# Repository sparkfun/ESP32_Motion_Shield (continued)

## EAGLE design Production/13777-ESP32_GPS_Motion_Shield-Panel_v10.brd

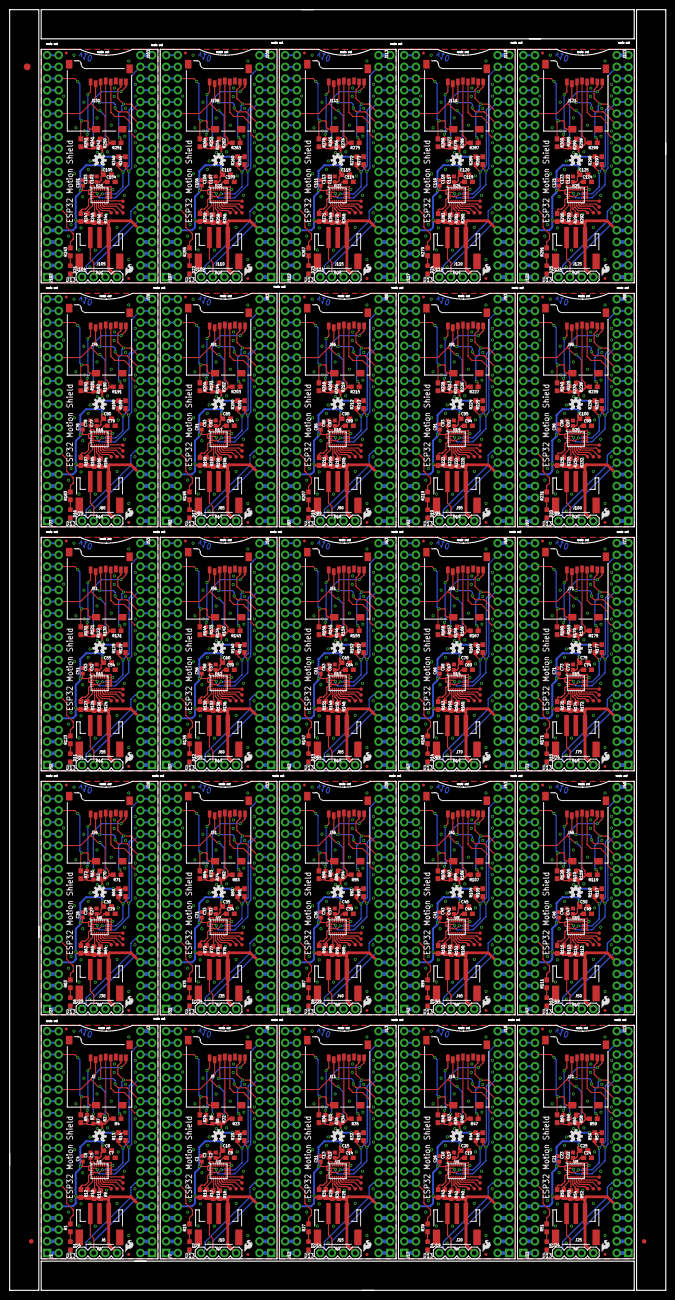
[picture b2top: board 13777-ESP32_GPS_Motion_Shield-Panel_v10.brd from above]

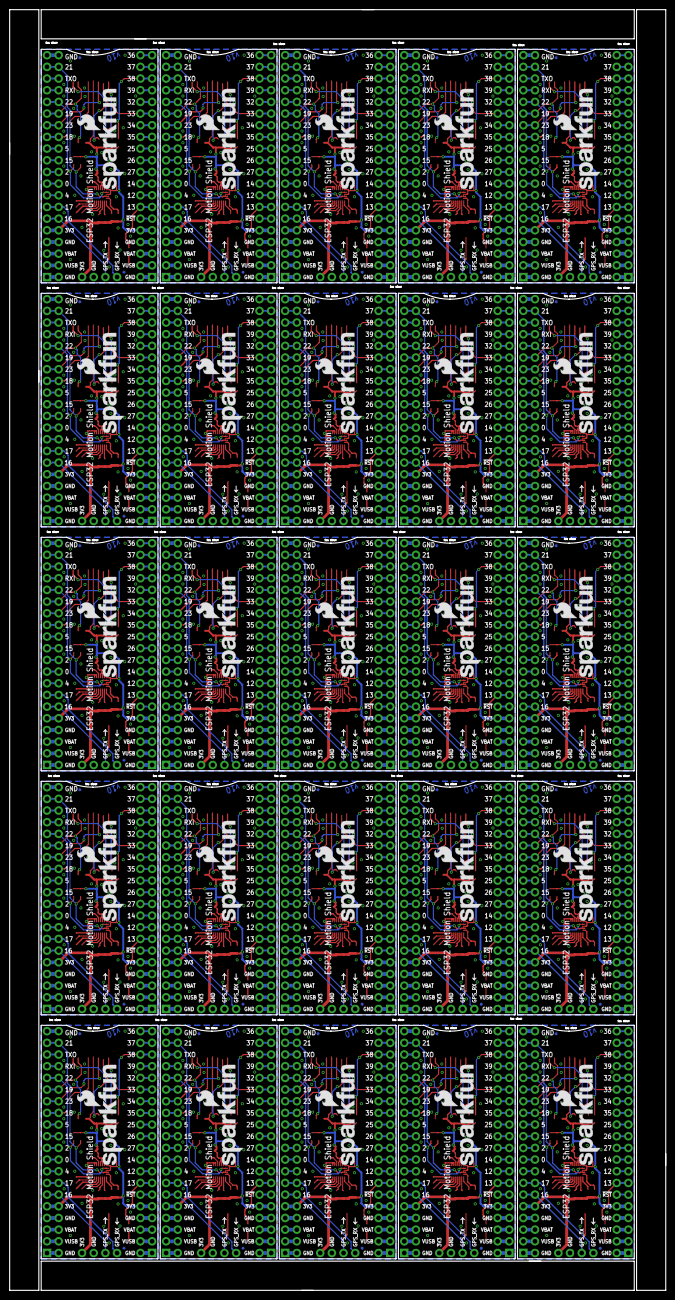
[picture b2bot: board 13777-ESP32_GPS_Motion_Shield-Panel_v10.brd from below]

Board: 2 copper layers, 142.7 x 278.6 mm, 928 parts (75 on the bottom side), 1225 nets.

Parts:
B1, B2, B3, B4, B5, B6, B7, B8, B9, B10, B11, B12, B13, B14, B15, B16, B17, B18, B19, B20, B21, B22, B23, B24, B25: ESP32_THING_WO_ANT_KEEPOUT; ESP32_THING_NO_ANT
C1, C2, C3, C4, C5, C6, C11, C12, C13, C16, C17, C18, C21, C22, C23, C26, C27, C28, C31, C32, C33, C36, C37, C38, C41, C42, C43, C46, C47, C48, C51, C52, C53, C56, C57, C58, C61, C62, C63, C66, C67, C68, C71, C72, C73, C76, C77, C78, C81, C82, C83, C86, C87, C88, C91, C92, C93, C96, C97, C98, C101, C102, C103, C106, C107, C108, C111, C112, C113, C116, C117, C118, C121, C122, C123: 0.1uF; 0402
C7, C9, C14, C19, C24, C29, C34, C39, C44, C49, C54, C59, C64, C69, C74, C79, C84, C89, C94, C99, C104, C109, C114, C119, C124: 10nF; 0603
C8, C10, C15, C20, C25, C30, C35, C40, C45, C50, C55, C60, C65, C70, C75, C80, C85, C90, C95, C100, C105, C110, C115, C120, C125: 10uF; 0603
D1, D2, D3, D4, D5, D6, D7, D8, D9, D10, D11, D12, D13, D14, D15, D16, D17, D18, D19, D20, D21, D22, D23, D24, D25: BLUE; LED-0603
E$1, E$2: FIDUCIAL-1X2
E$3: FIDUCIAL-1.5X3
FD1, FD2, FD3, FD4, FD5, FD6, FD7, FD8, FD9, FD10, FD11, FD12, FD13, FD14, FD15, FD16, FD17, FD18, FD19, FD20, FD21, FD22, FD23, FD24, FD25, FD26, FD27, FD28, FD29, FD30, FD31, FD32, FD33, FD34, FD35, FD36, FD37, FD38, FD39, FD40, FD41, FD42, FD43, FD44, FD45, FD46, FD47, FD48, FD49, FD50, FD51, FD52, FD53, FD54, FD55, FD56, FD57, FD58, FD59, FD60, FD61, FD62, FD63, FD64, FD65, FD66, FD67, FD68, FD69, FD70, FD71, FD72, FD73, FD74, FD75, FD76, FD77, FD78, FD79, FD80, FD81, FD82, FD83, FD84, FD85, FD86, FD87, FD88, FD89, FD90, FD91, FD92, FD93, FD94, FD95, FD96, FD97, FD98, FD99, FD100: FIDUCIALUFIDUCIAL; FIDUCIAL-MICRO
J1, J3, J7, J8, J12, J13, J17, J18, J22, J23, J27, J28, J32, J33, J37, J38, J42, J43, J47, J48, J52, J53, J57, J58, J62, J63, J67, J68, J72, J73, J77, J78, J82, J83, J87, J88, J92, J93, J97, J98, J102, J103, J107, J108, J112, J113, J117, J118, J122, J123: 1X20_NOSILK
J2, J5, J11, J16, J21, J26, J31, J36, J41, J46, J51, J56, J61, J66, J71, J76, J81, J86, J91, J96, J101, J106, J111, J116, J121: MICRO-SD_CARD_SOCKET; MICRO-SD-SOCKET
J4, J9, J14, J19, J24, J29, J34, J39, J44, J49, J54, J59, J64, J69, J74, J79, J84, J89, J94, J99, J104, J109, J114, J119, J124: 1X04
J6, J10, J15, J20, J25, J30, J35, J40, J45, J50, J55, J60, J65, J70, J75, J80, J85, J90, J95, J100, J105, J110, J115, J120, J125: 3-PIN SMD; JST-3-SMD
LOGO1, LOGO4, LOGO7, LOGO10, LOGO13, LOGO16, LOGO19, LOGO22, LOGO25, LOGO28, LOGO31, LOGO34, LOGO37, LOGO40, LOGO43, LOGO46, LOGO49, LOGO52, LOGO55, LOGO58, LOGO61, LOGO64, LOGO67, LOGO70, LOGO73: OSHW-LOGOS; OSHW-LOGO-S
LOGO2, LOGO6, LOGO9, LOGO12, LOGO15, LOGO18, LOGO21, LOGO24, LOGO27, LOGO30, LOGO33, LOGO36, LOGO39, LOGO42, LOGO45, LOGO48, LOGO51, LOGO54, LOGO57, LOGO60, LOGO63, LOGO66, LOGO69, LOGO72, LOGO75: SFE_LOGO_NAME_FLAME.2_INCH; SFE_LOGO_NAME_FLAME_.2
LOGO3, LOGO5, LOGO8, LOGO11, LOGO14, LOGO17, LOGO20, LOGO23, LOGO26, LOGO29, LOGO32, LOGO35, LOGO38, LOGO41, LOGO44, LOGO47, LOGO50, LOGO53, LOGO56, LOGO59, LOGO62, LOGO65, LOGO68, LOGO71, LOGO74: SFE_LOGO_FLAME.1_INCH; SFE_LOGO_FLAME_.1
R1, R15, R27, R39, R51, R63, R75, R87, R99, R111, R123, R135, R147, R159, R171, R183, R195, R207, R219, R231, R243, R255, R267, R279, R291: 470; 0603
R2, R4, R5, R9, R10, R11, R12, R16, R17, R18, R19, R22, R23, R24, R28, R29, R30, R31, R34, R35, R36, R40, R41, R42, R43, R46, R47, R48, R52, R53, R54, R55, R58, R59, R60, R64, R65, R66, R67, R70, R71, R72, R76, R77, R78, R79, R82, R83, R84, R88, R89, R90, R91, R94, R95, R96, R100, R101, R102, R103, R106, R107, R108, R112, R113, R114, R115, R118, R119, R120, R124, R125, R126, R127, R130, R131, R132, R136, R137, R138, R139, R142, R143, R144, R148, R149, R150, R151, R154, R155, R156, R160, R161, R162, R163, R166, R167, R168, R172, R173, R174, R175, R178, R179, R180, R184, R185, R186, R187, R190, R191, R192, R196, R197, R198, R199, R202, R203, R204, R208, R209, R210, R211, R214, R215, R216, R220, R221, R222, R223, R226, R227, R228, R232, R233, R234, R235, R238, R239, R240, R244, R245, R246, R247, R250, R251, R252, R256, R257, R258, R259, R262, R263, R264, R268, R269, R270, R271, R274, R275, R276, R280, R281, R282, R283, R286, R287, R288, R292, R293, R294, R295, R298, R299, R300: 10k; 0603
R3, R6, R7, R8, R25, R26, R37, R38, R49, R50, R61, R62, R73, R74, R85, R86, R97, R98, R109, R110, R121, R122, R133, R134, R145, R146, R157, R158, R169, R170, R181, R182, R193, R194, R205, R206, R217, R218, R229, R230, R241, R242, R253, R254, R265, R266, R277, R278, R289, R290: 100K; 0402
R13, R14, R20, R21, R32, R33, R44, R45, R56, R57, R68, R69, R80, R81, R92, R93, R104, R105, R116, R117, R128, R129, R140, R141, R152, R153, R164, R165, R176, R177, R188, R189, R200, R201, R212, R213, R224, R225, R236, R237, R248, R249, R260, R261, R272, R273, R284, R285, R296, R297: 4.7k; 0603
TP1, TP2, TP3, TP4, TP5, TP6, TP7, TP8, TP9, TP10, TP11, TP12, TP13, TP14, TP15, TP16, TP17, TP18, TP19, TP20, TP21, TP22, TP23, TP24, TP25, TP26, TP27, TP28, TP29, TP30, TP31, TP32, TP33, TP34, TP35, TP36, TP37, TP38, TP39, TP40, TP41, TP42, TP43, TP44, TP45, TP46, TP47, TP48, TP49, TP50, TP51, TP52, TP53, TP54, TP55, TP56, TP57, TP58, TP59, TP60, TP61, TP62, TP63, TP64, TP65, TP66, TP67, TP68, TP69, TP70, TP71, TP72, TP73, TP74, TP75, TP76, TP77, TP78, TP79, TP80, TP81, TP82, TP83, TP84, TP85, TP86, TP87, TP88, TP89, TP90, TP91, TP92, TP93, TP94, TP95, TP96, TP97, TP98, TP99, TP100, TP101, TP102, TP103, TP104, TP105, TP106, TP107, TP108, TP109, TP110, TP111, TP112, TP113, TP114, TP115, TP116, TP117, TP118, TP119, TP120, TP121, TP122, TP123, TP124, TP125: TEST-POINT3; PAD.03X.03
U1, U2, U3, U4, U5, U6, U7, U8, U9, U10, U11, U12, U13, U14, U15, U16, U17, U18, U19, U20, U21, U22, U23, U24, U25: LSM9DS1; LGA-24-3.5X3

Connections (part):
3.3V: B1.5, B1.36, C4.1, C5.1, C8.1, J1.5, J2.VCC, J3.16, J4.4, J6.3, R2.2, R3.2, R4.2, R5.2, R7.2, R9.2, R10.2, R11.2, R12.2, R13.2, R14.2, U1.1, U1.3, U1.22, U1.23
3.3V1: B2.5, B2.36, C1.1, C2.1, C10.1, J5.VCC, J7.5, J8.16, J9.4, J10.3, R6.2, R8.2, R16.2, R17.2, R18.2, R19.2, R20.2, R21.2, R22.2, R23.2, R24.2, U2.1, U2.3, U2.22, U2.23
3.3V2: B3.5, B3.36, C11.1, C12.1, C15.1, J11.VCC, J12.5, J13.16, J14.4, J15.3, R25.2, R26.2, R28.2, R29.2, R30.2, R31.2, R32.2, R33.2, R34.2, R35.2, R36.2, U3.1, U3.3, U3.22, U3.23
3.3V3: B4.5, B4.36, C16.1, C17.1, C20.1, J16.VCC, J17.5, J18.16, J19.4, J20.3, R37.2, R38.2, R40.2, R41.2, R42.2, R43.2, R44.2, R45.2, R46.2, R47.2, R48.2, U4.1, U4.3, U4.22, U4.23
3.3V4: B5.5, B5.36, C21.1, C22.1, C25.1, J21.VCC, J22.5, J23.16, J24.4, J25.3, R49.2, R50.2, R52.2, R53.2, R54.2, R55.2, R56.2, R57.2, R58.2, R59.2, R60.2, U5.1, U5.3, U5.22, U5.23
3.3V5: B6.5, B6.36, C26.1, C27.1, C30.1, J26.VCC, J27.5, J28.16, J29.4, J30.3, R61.2, R62.2, R64.2, R65.2, R66.2, R67.2, R68.2, R69.2, R70.2, R71.2, R72.2, U6.1, U6.3, U6.22, U6.23
3.3V6: B7.5, B7.36, C31.1, C32.1, C35.1, J31.VCC, J32.5, J33.16, J34.4, J35.3, R73.2, R74.2, R76.2, R77.2, R78.2, R79.2, R80.2, R81.2, R82.2, R83.2, R84.2, U7.1, U7.3, U7.22, U7.23
3.3V7: B8.5, B8.36, C36.1, C37.1, C40.1, J36.VCC, J37.5, J38.16, J39.4, J40.3, R85.2, R86.2, R88.2, R89.2, R90.2, R91.2, R92.2, R93.2, R94.2, R95.2, R96.2, U8.1, U8.3, U8.22, U8.23
3.3V8: B9.5, B9.36, C41.1, C42.1, C45.1, J41.VCC, J42.5, J43.16, J44.4, J45.3, R97.2, R98.2, R100.2, R101.2, R102.2, R103.2, R104.2, R105.2, R106.2, R107.2, R108.2, U9.1, U9.3, U9.22, U9.23
3.3V9: B10.5, B10.36, C46.1, C47.1, C50.1, J46.VCC, J47.5, J48.16, J49.4, J50.3, R109.2, R110.2, R112.2, R113.2, R114.2, R115.2, R116.2, R117.2, R118.2, R119.2, R120.2, U10.1, U10.3, U10.22, U10.23
3.3V10: B11.5, B11.36, C51.1, C52.1, C55.1, J51.VCC, J52.5, J53.16, J54.4, J55.3, R121.2, R122.2, R124.2, R125.2, R126.2, R127.2, R128.2, R129.2, R130.2, R131.2, R132.2, U11.1, U11.3, U11.22, U11.23
3.3V11: B12.5, B12.36, C56.1, C57.1, C60.1, J56.VCC, J57.5, J58.16, J59.4, J60.3, R133.2, R134.2, R136.2, R137.2, R138.2, R139.2, R140.2, R141.2, R142.2, R143.2, R144.2, U12.1, U12.3, U12.22, U12.23
3.3V12: B13.5, B13.36, C61.1, C62.1, C65.1, J61.VCC, J62.5, J63.16, J64.4, J65.3, R145.2, R146.2, R148.2, R149.2, R150.2, R151.2, R152.2, R153.2, R154.2, R155.2, R156.2, U13.1, U13.3, U13.22, U13.23
3.3V13: B14.5, B14.36, C66.1, C67.1, C70.1, J66.VCC, J67.5, J68.16, J69.4, J70.3, R157.2, R158.2, R160.2, R161.2, R162.2, R163.2, R164.2, R165.2, R166.2, R167.2, R168.2, U14.1, U14.3, U14.22, U14.23
3.3V14: B15.5, B15.36, C71.1, C72.1, C75.1, J71.VCC, J72.5, J73.16, J74.4, J75.3, R169.2, R170.2, R172.2, R173.2, R174.2, R175.2, R176.2, R177.2, R178.2, R179.2, R180.2, U15.1, U15.3, U15.22, U15.23
3.3V15: B16.5, B16.36, C76.1, C77.1, C80.1, J76.VCC, J77.5, J78.16, J79.4, J80.3, R181.2, R182.2, R184.2, R185.2, R186.2, R187.2, R188.2, R189.2, R190.2, R191.2, R192.2, U16.1, U16.3, U16.22, U16.23
3.3V16: B17.5, B17.36, C81.1, C82.1, C85.1, J81.VCC, J82.5, J83.16, J84.4, J85.3, R193.2, R194.2, R196.2, R197.2, R198.2, R199.2, R200.2, R201.2, R202.2, R203.2, R204.2, U17.1, U17.3, U17.22, U17.23
3.3V17: B18.5, B18.36, C86.1, C87.1, C90.1, J86.VCC, J87.5, J88.16, J89.4, J90.3, R205.2, R206.2, R208.2, R209.2, R210.2, R211.2, R212.2, R213.2, R214.2, R215.2, R216.2, U18.1, U18.3, U18.22, U18.23
3.3V18: B19.5, B19.36, C91.1, C92.1, C95.1, J91.VCC, J92.5, J93.16, J94.4, J95.3, R217.2, R218.2, R220.2, R221.2, R222.2, R223.2, R224.2, R225.2, R226.2, R227.2, R228.2, U19.1, U19.3, U19.22, U19.23
3.3V19: B20.5, B20.36, C96.1, C97.1, C100.1, J96.VCC, J97.5, J98.16, J99.4, J100.3, R229.2, R230.2, R232.2, R233.2, R234.2, R235.2, R236.2, R237.2, R238.2, R239.2, R240.2, U20.1, U20.3, U20.22, U20.23
3.3V20: B21.5, B21.36, C101.1, C102.1, C105.1, J101.VCC, J102.5, J103.16, J104.4, J105.3, R241.2, R242.2, R244.2, R245.2, R246.2, R247.2, R248.2, R249.2, R250.2, R251.2, R252.2, U21.1, U21.3, U21.22, U21.23
3.3V21: B22.5, B22.36, C106.1, C107.1, C110.1, J106.VCC, J107.5, J108.16, J109.4, J110.3, R253.2, R254.2, R256.2, R257.2, R258.2, R259.2, R260.2, R261.2, R262.2, R263.2, R264.2, U22.1, U22.3, U22.22, U22.23
3.3V22: B23.5, B23.36, C111.1, C112.1, C115.1, J111.VCC, J112.5, J113.16, J114.4, J115.3, R265.2, R266.2, R268.2, R269.2, R270.2, R271.2, R272.2, R273.2, R274.2, R275.2, R276.2, U23.1, U23.3, U23.22, U23.23
3.3V23: B24.5, B24.36, C116.1, C117.1, C120.1, J116.VCC, J117.5, J118.16, J119.4, J120.3, R277.2, R278.2, R280.2, R281.2, R282.2, R283.2, R284.2, R285.2, R286.2, R287.2, R288.2, U24.1, U24.3, U24.22, U24.23
3.3V24: B25.5, B25.36, C121.1, C122.1, C125.1, J121.VCC, J122.5, J123.16, J124.4, J125.3, R289.2, R290.2, R292.2, R293.2, R294.2, R295.2, R296.2, R297.2, R298.2, R299.2, R300.2, U25.1, U25.3, U25.22, U25.23
C1: C6.1, U1.24
C2: C3.1, U2.24
C3: C13.1, U3.24
C4: C18.1, U4.24
C5: C23.1, U5.24
C6: C28.1, U6.24
C7: C33.1, U7.24
C8: C38.1, U8.24
C9: C43.1, U9.24
C10: C48.1, U10.24
C11: C53.1, U11.24
C12: C58.1, U12.24
C13: C63.1, U13.24
C14: C68.1, U14.24
C15: C73.1, U15.24
C16: C78.1, U16.24
C17: C83.1, U17.24
C18: C88.1, U18.24
C19: C93.1, U19.24
C20: C98.1, U20.24
C21: C103.1, U21.24
C22: C108.1, U22.24
C23: C113.1, U23.24
C24: C118.1, U24.24
C25: C123.1, U25.24
CAP: C7.1, U1.21
CAP1: C9.1, U2.21
CAP2: C14.1, U3.21
CAP3: C19.1, U4.21
CAP4: C24.1, U5.21
CAP5: C29.1, U6.21
CAP6: C34.1, U7.21
CAP7: C39.1, U8.21
CAP8: C44.1, U9.21
CAP9: C49.1, U10.21
CAP10: C54.1, U11.21
CAP11: C59.1, U12.21
CAP12: C64.1, U13.21
CAP13: C69.1, U14.21
CAP14: C74.1, U15.21
CAP15: C79.1, U16.21
CAP16: C84.1, U17.21
CAP17: C89.1, U18.21
CAP18: C94.1, U19.21
CAP19: C99.1, U20.21
CAP20: C104.1, U21.21
CAP21: C109.1, U22.21
CAP22: C114.1, U23.21
CAP23: C119.1, U24.21
CAP24: C124.1, U25.21
CS_A/G: R11.1, U1.7
CS_A/G1: R18.1, U2.7
CS_A/G2: R30.1, U3.7
CS_A/G3: R42.1, U4.7
CS_A/G4: R54.1, U5.7
CS_A/G5: R66.1, U6.7
CS_A/G6: R78.1, U7.7
CS_A/G7: R90.1, U8.7
CS_A/G8: R102.1, U9.7
CS_A/G9: R114.1, U10.7
CS_A/G10: R126.1, U11.7
CS_A/G11: R138.1, U12.7
CS_A/G12: R150.1, U13.7
CS_A/G13: R162.1, U14.7
CS_A/G14: R174.1, U15.7
CS_A/G15: R186.1, U16.7
CS_A/G16: R198.1, U17.7
CS_A/G17: R210.1, U18.7
CS_A/G18: R222.1, U19.7
CS_A/G19: R234.1, U20.7
CS_A/G20: R246.1, U21.7
CS_A/G21: R258.1, U22.7
CS_A/G22: R270.1, U23.7
CS_A/G23: R282.1, U24.7
CS_A/G24: R294.1, U25.7
CS_M: R9.1, U1.8
CS_M1: R16.1, U2.8
CS_M2: R28.1, U3.8
CS_M3: R40.1, U4.8
CS_M4: R52.1, U5.8
CS_M5: R64.1, U6.8
CS_M6: R76.1, U7.8
CS_M7: R88.1, U8.8
CS_M8: R100.1, U9.8
CS_M9: R112.1, U10.8
CS_M10: R124.1, U11.8
CS_M11: R136.1, U12.8
CS_M12: R148.1, U13.8
CS_M13: R160.1, U14.8
CS_M14: R172.1, U15.8
CS_M15: R184.1, U16.8
CS_M16: R196.1, U17.8
CS_M17: R208.1, U18.8
CS_M18: R220.1, U19.8
CS_M19: R232.1, U20.8
CS_M20: R244.1, U21.8
CS_M21: R256.1, U22.8
CS_M22: R268.1, U23.8
CS_M23: R280.1, U24.8
CS_M24: R292.1, U25.8
DEN_A/G: TP3.P$1, U1.13
DEN_A/G1: TP8.P$1, U2.13
DEN_A/G2: TP13.P$1, U3.13
DEN_A/G3: TP18.P$1, U4.13
DEN_A/G4: TP23.P$1, U5.13
DEN_A/G5: TP28.P$1, U6.13
DEN_A/G6: TP33.P$1, U7.13
DEN_A/G7: TP38.P$1, U8.13
DEN_A/G8: TP43.P$1, U9.13
DEN_A/G9: TP48.P$1, U10.13
DEN_A/G10: TP53.P$1, U11.13
DEN_A/G11: TP58.P$1, U12.13
DEN_A/G12: TP63.P$1, U13.13
DEN_A/G13: TP68.P$1, U14.13
DEN_A/G14: TP73.P$1, U15.13
DEN_A/G15: TP78.P$1, U16.13
DEN_A/G16: TP83.P$1, U17.13
DEN_A/G17: TP88.P$1, U18.13
DEN_A/G18: TP93.P$1, U19.13
DEN_A/G19: TP98.P$1, U20.13
DEN_A/G20: TP103.P$1, U21.13
DEN_A/G21: TP108.P$1, U22.13
DEN_A/G22: TP113.P$1, U23.13
DEN_A/G23: TP118.P$1, U24.13
DEN_A/G24: TP123.P$1, U25.13
DRDY_M: TP4.P$1, U1.9
DRDY_M1: TP9.P$1, U2.9
DRDY_M2: TP14.P$1, U3.9
DRDY_M3: TP19.P$1, U4.9
DRDY_M4: TP24.P$1, U5.9
DRDY_M5: TP29.P$1, U6.9
DRDY_M6: TP34.P$1, U7.9
DRDY_M7: TP39.P$1, U8.9
DRDY_M8: TP44.P$1, U9.9
DRDY_M9: TP49.P$1, U10.9
DRDY_M10: TP54.P$1, U11.9
DRDY_M11: TP59.P$1, U12.9
DRDY_M12: TP64.P$1, U13.9
DRDY_M13: TP69.P$1, U14.9
DRDY_M14: TP74.P$1, U15.9
DRDY_M15: TP79.P$1, U16.9
DRDY_M16: TP84.P$1, U17.9
DRDY_M17: TP89.P$1, U18.9
DRDY_M18: TP94.P$1, U19.9
DRDY_M19: TP99.P$1, U20.9
DRDY_M20: TP104.P$1, U21.9
DRDY_M21: TP109.P$1, U22.9
DRDY_M22: TP114.P$1, U23.9
DRDY_M23: TP119.P$1, U24.9
DRDY_M24: TP124.P$1, U25.9
GND: B1.1, B1.4, B1.21, B1.37, B1.40, C4.2, C5.2, C6.2, C7.2, C8.2, D1.C, J1.1, J1.4, J2.GND, J2.GND1, J2.GND3, J3.1, J3.17, J3.20, J4.3, J6.2, U1.14, U1.15, U1.16, U1.17, U1.18, U1.19, U1.20
GND1: B2.1, B2.4, B2.21, B2.37, B2.40, C1.2, C2.2, C3.2, C9.2, C10.2, D2.C, J5.GND, J5.GND1, J5.GND3, J7.1, J7.4, J8.1, J8.17, J8.20, J9.3, J10.2, U2.14, U2.15, U2.16, U2.17, U2.18, U2.19, U2.20
GND2: B3.1, B3.4, B3.21, B3.37, B3.40, C11.2, C12.2, C13.2, C14.2, C15.2, D3.C, J11.GND, J11.GND1, J11.GND3, J12.1, J12.4, J13.1, J13.17, J13.20, J14.3, J15.2, U3.14, U3.15, U3.16, U3.17, U3.18, U3.19, U3.20
GND3: B4.1, B4.4, B4.21, B4.37, B4.40, C16.2, C17.2, C18.2, C19.2, C20.2, D4.C, J16.GND, J16.GND1, J16.GND3, J17.1, J17.4, J18.1, J18.17, J18.20, J19.3, J20.2, U4.14, U4.15, U4.16, U4.17, U4.18, U4.19, U4.20
GND4: B5.1, B5.4, B5.21, B5.37, B5.40, C21.2, C22.2, C23.2, C24.2, C25.2, D5.C, J21.GND, J21.GND1, J21.GND3, J22.1, J22.4, J23.1, J23.17, J23.20, J24.3, J25.2, U5.14, U5.15, U5.16, U5.17, U5.18, U5.19, U5.20
GND5: B6.1, B6.4, B6.21, B6.37, B6.40, C26.2, C27.2, C28.2, C29.2, C30.2, D6.C, J26.GND, J26.GND1, J26.GND3, J27.1, J27.4, J28.1, J28.17, J28.20, J29.3, J30.2, U6.14, U6.15, U6.16, U6.17, U6.18, U6.19, U6.20
GND6: B7.1, B7.4, B7.21, B7.37, B7.40, C31.2, C32.2, C33.2, C34.2, C35.2, D7.C, J31.GND, J31.GND1, J31.GND3, J32.1, J32.4, J33.1, J33.17, J33.20, J34.3, J35.2, U7.14, U7.15, U7.16, U7.17, U7.18, U7.19, U7.20
GND7: B8.1, B8.4, B8.21, B8.37, B8.40, C36.2, C37.2, C38.2, C39.2, C40.2, D8.C, J36.GND, J36.GND1, J36.GND3, J37.1, J37.4, J38.1, J38.17, J38.20, J39.3, J40.2, U8.14, U8.15, U8.16, U8.17, U8.18, U8.19, U8.20
GND8: B9.1, B9.4, B9.21, B9.37, B9.40, C41.2, C42.2, C43.2, C44.2, C45.2, D9.C, J41.GND, J41.GND1, J41.GND3, J42.1, J42.4, J43.1, J43.17, J43.20, J44.3, J45.2, U9.14, U9.15, U9.16, U9.17, U9.18, U9.19, U9.20
GND9: B10.1, B10.4, B10.21, B10.37, B10.40, C46.2, C47.2, C48.2, C49.2, C50.2, D10.C, J46.GND, J46.GND1, J46.GND3, J47.1, J47.4, J48.1, J48.17, J48.20, J49.3, J50.2, U10.14, U10.15, U10.16, U10.17, U10.18, U10.19, U10.20
GND10: B11.1, B11.4, B11.21, B11.37, B11.40, C51.2, C52.2, C53.2, C54.2, C55.2, D11.C, J51.GND, J51.GND1, J51.GND3, J52.1, J52.4, J53.1, J53.17, J53.20, J54.3, J55.2, U11.14, U11.15, U11.16, U11.17, U11.18, U11.19, U11.20
GND11: B12.1, B12.4, B12.21, B12.37, B12.40, C56.2, C57.2, C58.2, C59.2, C60.2, D12.C, J56.GND, J56.GND1, J56.GND3, J57.1, J57.4, J58.1, J58.17, J58.20, J59.3, J60.2, U12.14, U12.15, U12.16, U12.17, U12.18, U12.19, U12.20
GND12: B13.1, B13.4, B13.21, B13.37, B13.40, C61.2, C62.2, C63.2, C64.2, C65.2, D13.C, J61.GND, J61.GND1, J61.GND3, J62.1, J62.4, J63.1, J63.17, J63.20, J64.3, J65.2, U13.14, U13.15, U13.16, U13.17, U13.18, U13.19, U13.20
GND13: B14.1, B14.4, B14.21, B14.37, B14.40, C66.2, C67.2, C68.2, C69.2, C70.2, D14.C, J66.GND, J66.GND1, J66.GND3, J67.1, J67.4, J68.1, J68.17, J68.20, J69.3, J70.2, U14.14, U14.15, U14.16, U14.17, U14.18, U14.19, U14.20
GND14: B15.1, B15.4, B15.21, B15.37, B15.40, C71.2, C72.2, C73.2, C74.2, C75.2, D15.C, J71.GND, J71.GND1, J71.GND3, J72.1, J72.4, J73.1, J73.17, J73.20, J74.3, J75.2, U15.14, U15.15, U15.16, U15.17, U15.18, U15.19, U15.20
GND15: B16.1, B16.4, B16.21, B16.37, B16.40, C76.2, C77.2, C78.2, C79.2, C80.2, D16.C, J76.GND, J76.GND1, J76.GND3, J77.1, J77.4, J78.1, J78.17, J78.20, J79.3, J80.2, U16.14, U16.15, U16.16, U16.17, U16.18, U16.19, U16.20
GND16: B17.1, B17.4, B17.21, B17.37, B17.40, C81.2, C82.2, C83.2, C84.2, C85.2, D17.C, J81.GND, J81.GND1, J81.GND3, J82.1, J82.4, J83.1, J83.17, J83.20, J84.3, J85.2, U17.14, U17.15, U17.16, U17.17, U17.18, U17.19, U17.20
GND17: B18.1, B18.4, B18.21, B18.37, B18.40, C86.2, C87.2, C88.2, C89.2, C90.2, D18.C, J86.GND, J86.GND1, J86.GND3, J87.1, J87.4, J88.1, J88.17, J88.20, J89.3, J90.2, U18.14, U18.15, U18.16, U18.17, U18.18, U18.19, U18.20
GND18: B19.1, B19.4, B19.21, B19.37, B19.40, C91.2, C92.2, C93.2, C94.2, C95.2, D19.C, J91.GND, J91.GND1, J91.GND3, J92.1, J92.4, J93.1, J93.17, J93.20, J94.3, J95.2, U19.14, U19.15, U19.16, U19.17, U19.18, U19.19, U19.20
GND19: B20.1, B20.4, B20.21, B20.37, B20.40, C96.2, C97.2, C98.2, C99.2, C100.2, D20.C, J96.GND, J96.GND1, J96.GND3, J97.1, J97.4, J98.1, J98.17, J98.20, J99.3, J100.2, U20.14, U20.15, U20.16, U20.17, U20.18, U20.19, U20.20
GND20: B21.1, B21.4, B21.21, B21.37, B21.40, C101.2, C102.2, C103.2, C104.2, C105.2, D21.C, J101.GND, J101.GND1, J101.GND3, J102.1, J102.4, J103.1, J103.17, J103.20, J104.3, J105.2, U21.14, U21.15, U21.16, U21.17, U21.18, U21.19, U21.20
GND21: B22.1, B22.4, B22.21, B22.37, B22.40, C106.2, C107.2, C108.2, C109.2, C110.2, D22.C, J106.GND, J106.GND1, J106.GND3, J107.1, J107.4, J108.1, J108.17, J108.20, J109.3, J110.2, U22.14, U22.15, U22.16, U22.17, U22.18, U22.19, U22.20
GND22: B23.1, B23.4, B23.21, B23.37, B23.40, C111.2, C112.2, C113.2, C114.2, C115.2, D23.C, J111.GND, J111.GND1, J111.GND3, J112.1, J112.4, J113.1, J113.17, J113.20, J114.3, J115.2, U23.14, U23.15, U23.16, U23.17, U23.18, U23.19, U23.20
GND23: B24.1, B24.4, B24.21, B24.37, B24.40, C116.2, C117.2, C118.2, C119.2, C120.2, D24.C, J116.GND, J116.GND1, J116.GND3, J117.1, J117.4, J118.1, J118.17, J118.20, J119.3, J120.2, U24.14, U24.15, U24.16, U24.17, U24.18, U24.19, U24.20
GND24: B25.1, B25.4, B25.21, B25.37, B25.40, C121.2, C122.2, C123.2, C124.2, C125.2, D25.C, J121.GND, J121.GND1, J121.GND3, J122.1, J122.4, J123.1, J123.17, J123.20, J124.3, J125.2, U25.14, U25.15, U25.16, U25.17, U25.18, U25.19, U25.20
GPS_LED: B1.7, J1.7, R1.2
GPS_LED1: B2.7, J7.7, R15.2
GPS_LED2: B3.7, J12.7, R27.2
GPS_LED3: B4.7, J17.7, R39.2
GPS_LED4: B5.7, J22.7, R51.2
GPS_LED5: B6.7, J27.7, R63.2
GPS_LED6: B7.7, J32.7, R75.2
GPS_LED7: B8.7, J37.7, R87.2
GPS_LED8: B9.7, J42.7, R99.2
GPS_LED9: B10.7, J47.7, R111.2
GPS_LED10: B11.7, J52.7, R123.2
GPS_LED11: B12.7, J57.7, R135.2
GPS_LED12: B13.7, J62.7, R147.2
GPS_LED13: B14.7, J67.7, R159.2
GPS_LED14: B15.7, J72.7, R171.2
GPS_LED15: B16.7, J77.7, R183.2
GPS_LED16: B17.7, J82.7, R195.2
GPS_LED17: B18.7, J87.7, R207.2
GPS_LED18: B19.7, J92.7, R219.2
GPS_LED19: B20.7, J97.7, R231.2
GPS_LED20: B21.7, J102.7, R243.2
GPS_LED21: B22.7, J107.7, R255.2
GPS_LED22: B23.7, J112.7, R267.2
GPS_LED23: B24.7, J117.7, R279.2
GPS_LED24: B25.7, J122.7, R291.2
GPS_RX: B1.34, J3.14, J4.1
GPS_RX1: B2.34, J8.14, J9.1
GPS_RX2: B3.34, J13.14, J14.1
GPS_RX3: B4.34, J18.14, J19.1
GPS_RX4: B5.34, J23.14, J24.1
GPS_RX5: B6.34, J28.14, J29.1
GPS_RX6: B7.34, J33.14, J34.1
GPS_RX7: B8.34, J38.14, J39.1
GPS_RX8: B9.34, J43.14, J44.1
GPS_RX9: B10.34, J48.14, J49.1
GPS_RX10: B11.34, J53.14, J54.1
GPS_RX11: B12.34, J58.14, J59.1
GPS_RX12: B13.34, J63.14, J64.1
GPS_RX13: B14.34, J68.14, J69.1
GPS_RX14: B15.34, J73.14, J74.1
GPS_RX15: B16.34, J78.14, J79.1
GPS_RX16: B17.34, J83.14, J84.1
GPS_RX17: B18.34, J88.14, J89.1
GPS_RX18: B19.34, J93.14, J94.1
GPS_RX19: B20.34, J98.14, J99.1
GPS_RX20: B21.34, J103.14, J104.1
GPS_RX21: B22.34, J108.14, J109.1
GPS_RX22: B23.34, J113.14, J114.1
GPS_RX23: B24.34, J118.14, J119.1
GPS_RX24: B25.34, J123.14, J124.1
GPS_TX: B1.35, J3.15, J4.2, J6.1
GPS_TX1: B2.35, J8.15, J9.2, J10.1
GPS_TX2: B3.35, J13.15, J14.2, J15.1
GPS_TX3: B4.35, J18.15, J19.2, J20.1
GPS_TX4: B5.35, J23.15, J24.2, J25.1
GPS_TX5: B6.35, J28.15, J29.2, J30.1
GPS_TX6: B7.35, J33.15, J34.2, J35.1
GPS_TX7: B8.35, J38.15, J39.2, J40.1
GPS_TX8: B9.35, J43.15, J44.2, J45.1
GPS_TX9: B10.35, J48.15, J49.2, J50.1
GPS_TX10: B11.35, J53.15, J54.2, J55.1
GPS_TX11: B12.35, J58.15, J59.2, J60.1
GPS_TX12: B13.35, J63.15, J64.2, J65.1
GPS_TX13: B14.35, J68.15, J69.2, J70.1
GPS_TX14: B15.35, J73.15, J74.2, J75.1
GPS_TX15: B16.35, J78.15, J79.2, J80.1
GPS_TX16: B17.35, J83.15, J84.2, J85.1
GPS_TX17: B18.35, J88.15, J89.2, J90.1
GPS_TX18: B19.35, J93.15, J94.2, J95.1
GPS_TX19: B20.35, J98.15, J99.2, J100.1
GPS_TX20: B21.35, J103.15, J104.2, J105.1
GPS_TX21: B22.35, J108.15, J109.2, J110.1
GPS_TX22: B23.35, J113.15, J114.2, J115.1
GPS_TX23: B24.35, J118.15, J119.2, J120.1
GPS_TX24: B25.35, J123.15, J124.2, J125.1
INT1_A/G: TP1.P$1, U1.11
INT1_A/G1: TP6.P$1, U2.11
INT1_A/G2: TP11.P$1, U3.11
INT1_A/G3: TP16.P$1, U4.11
INT1_A/G4: TP21.P$1, U5.11
INT1_A/G5: TP26.P$1, U6.11
INT1_A/G6: TP31.P$1, U7.11
INT1_A/G7: TP36.P$1, U8.11
INT1_A/G8: TP41.P$1, U9.11
INT1_A/G9: TP46.P$1, U10.11
INT1_A/G10: TP51.P$1, U11.11
INT1_A/G11: TP56.P$1, U12.11
INT1_A/G12: TP61.P$1, U13.11
INT1_A/G13: TP66.P$1, U14.11
INT1_A/G14: TP71.P$1, U15.11
INT1_A/G15: TP76.P$1, U16.11
INT1_A/G16: TP81.P$1, U17.11
INT1_A/G17: TP86.P$1, U18.11
INT1_A/G18: TP91.P$1, U19.11
INT1_A/G19: TP96.P$1, U20.11
INT1_A/G20: TP101.P$1, U21.11
INT1_A/G21: TP106.P$1, U22.11
INT1_A/G22: TP111.P$1, U23.11
INT1_A/G23: TP116.P$1, U24.11
INT1_A/G24: TP121.P$1, U25.11
INT2_A/G: TP2.P$1, U1.12
INT2_A/G1: TP7.P$1, U2.12
INT2_A/G2: TP12.P$1, U3.12
INT2_A/G3: TP17.P$1, U4.12
INT2_A/G4: TP22.P$1, U5.12
INT2_A/G5: TP27.P$1, U6.12
INT2_A/G6: TP32.P$1, U7.12
INT2_A/G7: TP37.P$1, U8.12
INT2_A/G8: TP42.P$1, U9.12
INT2_A/G9: TP47.P$1, U10.12
INT2_A/G10: TP52.P$1, U11.12
INT2_A/G11: TP57.P$1, U12.12
INT2_A/G12: TP62.P$1, U13.12
INT2_A/G13: TP67.P$1, U14.12
INT2_A/G14: TP72.P$1, U15.12
INT2_A/G15: TP77.P$1, U16.12
INT2_A/G16: TP82.P$1, U17.12
INT2_A/G17: TP87.P$1, U18.12
INT2_A/G18: TP92.P$1, U19.12
INT2_A/G19: TP97.P$1, U20.12
INT2_A/G20: TP102.P$1, U21.12
INT2_A/G21: TP107.P$1, U22.12
INT2_A/G22: TP112.P$1, U23.12
INT2_A/G23: TP117.P$1, U24.12
INT2_A/G24: TP122.P$1, U25.12
INT_M: TP5.P$1, U1.10
INT_M1: TP10.P$1, U2.10
INT_M2: TP15.P$1, U3.10
INT_M3: TP20.P$1, U4.10
INT_M4: TP25.P$1, U5.10
INT_M5: TP30.P$1, U6.10
INT_M6: TP35.P$1, U7.10
INT_M7: TP40.P$1, U8.10
INT_M8: TP45.P$1, U9.10
INT_M9: TP50.P$1, U10.10
INT_M10: TP55.P$1, U11.10
INT_M11: TP60.P$1, U12.10
INT_M12: TP65.P$1, U13.10
INT_M13: TP70.P$1, U14.10
INT_M14: TP75.P$1, U15.10
INT_M15: TP80.P$1, U16.10
INT_M16: TP85.P$1, U17.10
INT_M17: TP90.P$1, U18.10
INT_M18: TP95.P$1, U19.10
INT_M19: TP100.P$1, U20.10
INT_M20: TP105.P$1, U21.10
INT_M21: TP110.P$1, U22.10
INT_M22: TP115.P$1, U23.10
INT_M23: TP120.P$1, U24.10
INT_M24: TP125.P$1, U25.10
unnamed: D1.A, R1.1
unnamed: B1.30, J3.10
unnamed: B1.17, J1.17
unnamed: B1.16, J1.16
unnamed: B1.19, J1.19
unnamed: B1.10, J1.10
unnamed: B1.14, J1.14
unnamed: D2.A, R15.1
unnamed: J2.RSV1, R3.1
unnamed: J2.RSV2, R7.1
unnamed: B2.6, J7.6
unnamed: B2.8, J7.8
unnamed: B2.9, J7.9
unnamed: B2.11, J7.11
unnamed: B1.6, J1.6
unnamed: B2.12, J7.12
unnamed: B1.8, J1.8
unnamed: B1.9, J1.9
unnamed: B2.13, J7.13
unnamed: B1.11, J1.11
unnamed: B1.12, J1.12
unnamed: B1.13, J1.13
unnamed: B1.20, J1.20
unnamed: B2.20, J7.20
unnamed: B2.23, J8.3
unnamed: B2.24, J8.4
unnamed: B2.29, J8.9
unnamed: B2.31, J8.11
unnamed: B2.32, J8.12
unnamed: B2.33, J8.13
unnamed: J5.RSV1, R6.1
unnamed: B1.23, J3.3
unnamed: B1.24, J3.4
unnamed: J5.RSV2, R8.1
unnamed: B2.30, J8.10
unnamed: B2.17, J7.17
unnamed: B2.16, J7.16
unnamed: B1.29, J3.9
unnamed: B2.19, J7.19
unnamed: B1.31, J3.11
unnamed: B1.32, J3.12
unnamed: B1.33, J3.13
unnamed: B2.10, J7.10
unnamed: B2.14, J7.14
unnamed: D3.A, R27.1
unnamed: B3.6, J12.6
unnamed: B3.8, J12.8
unnamed: B3.9, J12.9
unnamed: B3.11, J12.11
unnamed: B3.12, J12.12
unnamed: B3.13, J12.13
unnamed: B3.20, J12.20
unnamed: B3.23, J13.3
unnamed: B3.24, J13.4
unnamed: B3.29, J13.9
unnamed: B3.31, J13.11
unnamed: B3.32, J13.12
unnamed: B3.33, J13.13
unnamed: J11.RSV1, R25.1
unnamed: J11.RSV2, R26.1
unnamed: B3.30, J13.10
unnamed: B3.17, J12.17
unnamed: B3.16, J12.16
unnamed: B3.19, J12.19
unnamed: B3.10, J12.10
unnamed: B3.14, J12.14
unnamed: D4.A, R39.1
unnamed: B4.6, J17.6
unnamed: B4.8, J17.8
unnamed: B4.9, J17.9
unnamed: B4.11, J17.11
unnamed: B4.12, J17.12
unnamed: B4.13, J17.13
unnamed: B4.20, J17.20
unnamed: B4.23, J18.3
unnamed: B4.24, J18.4
unnamed: B4.29, J18.9
unnamed: B4.31, J18.11
unnamed: B4.32, J18.12
unnamed: B4.33, J18.13
unnamed: J16.RSV1, R37.1
unnamed: J16.RSV2, R38.1
unnamed: B4.30, J18.10
unnamed: B4.17, J17.17
unnamed: B4.16, J17.16
unnamed: B4.19, J17.19
unnamed: B4.10, J17.10
unnamed: B4.14, J17.14
unnamed: D5.A, R51.1
unnamed: B5.6, J22.6
unnamed: B5.8, J22.8
unnamed: B5.9, J22.9
unnamed: B5.11, J22.11
unnamed: B5.12, J22.12
unnamed: B5.13, J22.13
unnamed: B5.20, J22.20
unnamed: B5.23, J23.3
unnamed: B5.24, J23.4
unnamed: B5.29, J23.9
unnamed: B5.31, J23.11
unnamed: B5.32, J23.12
unnamed: B5.33, J23.13
unnamed: J21.RSV1, R49.1
unnamed: J21.RSV2, R50.1
unnamed: B5.30, J23.10
unnamed: B5.17, J22.17
unnamed: B5.16, J22.16
unnamed: B5.19, J22.19
unnamed: B5.10, J22.10
unnamed: B5.14, J22.14
unnamed: D6.A, R63.1
unnamed: B6.6, J27.6
unnamed: B6.8, J27.8
unnamed: B6.9, J27.9
unnamed: B6.11, J27.11
unnamed: B6.12, J27.12
unnamed: B6.13, J27.13
unnamed: B6.20, J27.20
unnamed: B6.23, J28.3
unnamed: B6.24, J28.4
unnamed: B6.29, J28.9
unnamed: B6.31, J28.11
unnamed: B6.32, J28.12
unnamed: B6.33, J28.13
unnamed: J26.RSV1, R61.1
unnamed: J26.RSV2, R62.1
unnamed: B6.30, J28.10
unnamed: B6.17, J27.17
unnamed: B6.16, J27.16
unnamed: B6.19, J27.19
unnamed: B6.10, J27.10
unnamed: B6.14, J27.14
unnamed: D7.A, R75.1
unnamed: B7.6, J32.6
unnamed: B7.8, J32.8
unnamed: B7.9, J32.9
unnamed: B7.11, J32.11
unnamed: B7.12, J32.12
unnamed: B7.13, J32.13
unnamed: B7.20, J32.20
unnamed: B7.23, J33.3
unnamed: B7.24, J33.4
unnamed: B7.29, J33.9
unnamed: B7.31, J33.11
unnamed: B7.32, J33.12
unnamed: B7.33, J33.13
unnamed: J31.RSV1, R73.1
unnamed: J31.RSV2, R74.1
unnamed: B7.30, J33.10
unnamed: B7.17, J32.17
unnamed: B7.16, J32.16
unnamed: B7.19, J32.19
unnamed: B7.10, J32.10
unnamed: B7.14, J32.14
unnamed: D8.A, R87.1
unnamed: B8.6, J37.6
unnamed: B8.8, J37.8
unnamed: B8.9, J37.9
unnamed: B8.11, J37.11
unnamed: B8.12, J37.12
unnamed: B8.13, J37.13
unnamed: B8.20, J37.20
unnamed: B8.23, J38.3
unnamed: B8.24, J38.4
unnamed: B8.29, J38.9
unnamed: B8.31, J38.11
unnamed: B8.32, J38.12
unnamed: B8.33, J38.13
unnamed: J36.RSV1, R85.1
unnamed: J36.RSV2, R86.1
unnamed: B8.30, J38.10
unnamed: B8.17, J37.17
unnamed: B8.16, J37.16
unnamed: B8.19, J37.19
unnamed: B8.10, J37.10
unnamed: B8.14, J37.14
unnamed: D9.A, R99.1
unnamed: B9.6, J42.6
unnamed: B9.8, J42.8
unnamed: B9.9, J42.9
unnamed: B9.11, J42.11
unnamed: B9.12, J42.12
unnamed: B9.13, J42.13
unnamed: B9.20, J42.20
unnamed: B9.23, J43.3
unnamed: B9.24, J43.4
unnamed: B9.29, J43.9
unnamed: B9.31, J43.11
unnamed: B9.32, J43.12
unnamed: B9.33, J43.13
unnamed: J41.RSV1, R97.1
unnamed: J41.RSV2, R98.1
unnamed: B9.30, J43.10
unnamed: B9.17, J42.17
unnamed: B9.16, J42.16
unnamed: B9.19, J42.19
unnamed: B9.10, J42.10
unnamed: B9.14, J42.14
unnamed: D10.A, R111.1
unnamed: B10.6, J47.6
unnamed: B10.8, J47.8
unnamed: B10.9, J47.9
unnamed: B10.11, J47.11
unnamed: B10.12, J47.12
unnamed: B10.13, J47.13
unnamed: B10.20, J47.20
unnamed: B10.23, J48.3
unnamed: B10.24, J48.4
unnamed: B10.29, J48.9
unnamed: B10.31, J48.11
unnamed: B10.32, J48.12
unnamed: B10.33, J48.13
unnamed: J46.RSV1, R109.1
unnamed: J46.RSV2, R110.1
unnamed: B10.30, J48.10
unnamed: B10.17, J47.17
unnamed: B10.16, J47.16
unnamed: B10.19, J47.19
unnamed: B10.10, J47.10
unnamed: B10.14, J47.14
unnamed: D11.A, R123.1
unnamed: B11.6, J52.6
unnamed: B11.8, J52.8
unnamed: B11.9, J52.9
unnamed: B11.11, J52.11
unnamed: B11.12, J52.12
unnamed: B11.13, J52.13
unnamed: B11.20, J52.20
unnamed: B11.23, J53.3
unnamed: B11.24, J53.4
unnamed: B11.29, J53.9
unnamed: B11.31, J53.11
unnamed: B11.32, J53.12
unnamed: B11.33, J53.13
unnamed: J51.RSV1, R121.1
unnamed: J51.RSV2, R122.1
unnamed: B11.30, J53.10
unnamed: B11.17, J52.17
unnamed: B11.16, J52.16
unnamed: B11.19, J52.19
unnamed: B11.10, J52.10
unnamed: B11.14, J52.14
unnamed: D12.A, R135.1
unnamed: B12.6, J57.6
unnamed: B12.8, J57.8
unnamed: B12.9, J57.9
unnamed: B12.11, J57.11
unnamed: B12.12, J57.12
unnamed: B12.13, J57.13
unnamed: B12.20, J57.20
unnamed: B12.23, J58.3
unnamed: B12.24, J58.4
unnamed: B12.29, J58.9
unnamed: B12.31, J58.11
unnamed: B12.32, J58.12
unnamed: B12.33, J58.13
unnamed: J56.RSV1, R133.1
unnamed: J56.RSV2, R134.1
unnamed: B12.30, J58.10
unnamed: B12.17, J57.17
unnamed: B12.16, J57.16
unnamed: B12.19, J57.19
unnamed: B12.10, J57.10
unnamed: B12.14, J57.14
unnamed: D13.A, R147.1
unnamed: B13.6, J62.6
unnamed: B13.8, J62.8
unnamed: B13.9, J62.9
unnamed: B13.11, J62.11
unnamed: B13.12, J62.12
unnamed: B13.13, J62.13
unnamed: B13.20, J62.20
unnamed: B13.23, J63.3
unnamed: B13.24, J63.4
unnamed: B13.29, J63.9
unnamed: B13.31, J63.11
unnamed: B13.32, J63.12
unnamed: B13.33, J63.13
unnamed: J61.RSV1, R145.1
unnamed: J61.RSV2, R146.1
unnamed: B13.30, J63.10
unnamed: B13.17, J62.17
unnamed: B13.16, J62.16
unnamed: B13.19, J62.19
unnamed: B13.10, J62.10
unnamed: B13.14, J62.14
unnamed: D14.A, R159.1
unnamed: B14.6, J67.6
unnamed: B14.8, J67.8
unnamed: B14.9, J67.9
unnamed: B14.11, J67.11
unnamed: B14.12, J67.12
unnamed: B14.13, J67.13
unnamed: B14.20, J67.20
unnamed: B14.23, J68.3
unnamed: B14.24, J68.4
unnamed: B14.29, J68.9
unnamed: B14.31, J68.11
unnamed: B14.32, J68.12
unnamed: B14.33, J68.13
unnamed: J66.RSV1, R157.1
unnamed: J66.RSV2, R158.1
unnamed: B14.30, J68.10
unnamed: B14.17, J67.17
unnamed: B14.16, J67.16
unnamed: B14.19, J67.19
unnamed: B14.10, J67.10
unnamed: B14.14, J67.14
unnamed: D15.A, R171.1
unnamed: B15.6, J72.6
unnamed: B15.8, J72.8
unnamed: B15.9, J72.9
unnamed: B15.11, J72.11
unnamed: B15.12, J72.12
unnamed: B15.13, J72.13
unnamed: B15.20, J72.20
unnamed: B15.23, J73.3
unnamed: B15.24, J73.4
unnamed: B15.29, J73.9
unnamed: B15.31, J73.11
unnamed: B15.32, J73.12
unnamed: B15.33, J73.13
unnamed: J71.RSV1, R169.1
unnamed: J71.RSV2, R170.1
unnamed: B15.30, J73.10
unnamed: B15.17, J72.17
unnamed: B15.16, J72.16
unnamed: B15.19, J72.19
unnamed: B15.10, J72.10
unnamed: B15.14, J72.14
unnamed: D16.A, R183.1
unnamed: B16.6, J77.6
unnamed: B16.8, J77.8
unnamed: B16.9, J77.9
unnamed: B16.11, J77.11
unnamed: B16.12, J77.12
unnamed: B16.13, J77.13
unnamed: B16.20, J77.20
unnamed: B16.23, J78.3
unnamed: B16.24, J78.4
unnamed: B16.29, J78.9
unnamed: B16.31, J78.11
unnamed: B16.32, J78.12
unnamed: B16.33, J78.13
unnamed: J76.RSV1, R181.1
unnamed: J76.RSV2, R182.1
unnamed: B16.30, J78.10
unnamed: B16.17, J77.17
unnamed: B16.16, J77.16
unnamed: B16.19, J77.19
unnamed: B16.10, J77.10
unnamed: B16.14, J77.14
unnamed: D17.A, R195.1
unnamed: B17.6, J82.6
unnamed: B17.8, J82.8
unnamed: B17.9, J82.9
unnamed: B17.11, J82.11
unnamed: B17.12, J82.12
unnamed: B17.13, J82.13
unnamed: B17.20, J82.20
unnamed: B17.23, J83.3
unnamed: B17.24, J83.4
unnamed: B17.29, J83.9
unnamed: B17.31, J83.11
unnamed: B17.32, J83.12
unnamed: B17.33, J83.13
unnamed: J81.RSV1, R193.1
unnamed: J81.RSV2, R194.1
unnamed: B17.30, J83.10
unnamed: B17.17, J82.17
unnamed: B17.16, J82.16
unnamed: B17.19, J82.19
unnamed: B17.10, J82.10
unnamed: B17.14, J82.14
unnamed: D18.A, R207.1
unnamed: B18.6, J87.6
unnamed: B18.8, J87.8
unnamed: B18.9, J87.9
unnamed: B18.11, J87.11
unnamed: B18.12, J87.12
unnamed: B18.13, J87.13
unnamed: B18.20, J87.20
unnamed: B18.23, J88.3
unnamed: B18.24, J88.4
unnamed: B18.29, J88.9
unnamed: B18.31, J88.11
unnamed: B18.32, J88.12
unnamed: B18.33, J88.13
unnamed: J86.RSV1, R205.1
unnamed: J86.RSV2, R206.1
unnamed: B18.30, J88.10
unnamed: B18.17, J87.17
unnamed: B18.16, J87.16
unnamed: B18.19, J87.19
unnamed: B18.10, J87.10
unnamed: B18.14, J87.14
unnamed: D19.A, R219.1
unnamed: B19.6, J92.6
unnamed: B19.8, J92.8
unnamed: B19.9, J92.9
unnamed: B19.11, J92.11
unnamed: B19.12, J92.12
unnamed: B19.13, J92.13
unnamed: B19.20, J92.20
unnamed: B19.23, J93.3
unnamed: B19.24, J93.4
unnamed: B19.29, J93.9
unnamed: B19.31, J93.11
unnamed: B19.32, J93.12
unnamed: B19.33, J93.13
unnamed: J91.RSV1, R217.1
unnamed: J91.RSV2, R218.1
unnamed: B19.30, J93.10
unnamed: B19.17, J92.17
unnamed: B19.16, J92.16
unnamed: B19.19, J92.19
unnamed: B19.10, J92.10
unnamed: B19.14, J92.14
unnamed: D20.A, R231.1
unnamed: B20.6, J97.6
unnamed: B20.8, J97.8
unnamed: B20.9, J97.9
unnamed: B20.11, J97.11
unnamed: B20.12, J97.12
unnamed: B20.13, J97.13
unnamed: B20.20, J97.20
unnamed: B20.23, J98.3
unnamed: B20.24, J98.4
unnamed: B20.29, J98.9
unnamed: B20.31, J98.11
unnamed: B20.32, J98.12
unnamed: B20.33, J98.13
unnamed: J96.RSV1, R229.1
unnamed: J96.RSV2, R230.1
unnamed: B20.30, J98.10
unnamed: B20.17, J97.17
unnamed: B20.16, J97.16
unnamed: B20.19, J97.19
unnamed: B20.10, J97.10
unnamed: B20.14, J97.14
unnamed: D21.A, R243.1
unnamed: B21.6, J102.6
unnamed: B21.8, J102.8
unnamed: B21.9, J102.9
unnamed: B21.11, J102.11
unnamed: B21.12, J102.12
unnamed: B21.13, J102.13
unnamed: B21.20, J102.20
unnamed: B21.23, J103.3
unnamed: B21.24, J103.4
unnamed: B21.29, J103.9
unnamed: B21.31, J103.11
unnamed: B21.32, J103.12
unnamed: B21.33, J103.13
unnamed: J101.RSV1, R241.1
unnamed: J101.RSV2, R242.1
unnamed: B21.30, J103.10
unnamed: B21.17, J102.17
unnamed: B21.16, J102.16
unnamed: B21.19, J102.19
unnamed: B21.10, J102.10
unnamed: B21.14, J102.14
unnamed: D22.A, R255.1
unnamed: B22.6, J107.6
unnamed: B22.8, J107.8
unnamed: B22.9, J107.9
unnamed: B22.11, J107.11
unnamed: B22.12, J107.12
unnamed: B22.13, J107.13
unnamed: B22.20, J107.20
unnamed: B22.23, J108.3
unnamed: B22.24, J108.4
unnamed: B22.29, J108.9
unnamed: B22.31, J108.11
unnamed: B22.32, J108.12
unnamed: B22.33, J108.13
unnamed: J106.RSV1, R253.1
unnamed: J106.RSV2, R254.1
unnamed: B22.30, J108.10
unnamed: B22.17, J107.17
unnamed: B22.16, J107.16
unnamed: B22.19, J107.19
unnamed: B22.10, J107.10
unnamed: B22.14, J107.14
unnamed: D23.A, R267.1
unnamed: B23.6, J112.6
unnamed: B23.8, J112.8
unnamed: B23.9, J112.9
unnamed: B23.11, J112.11
unnamed: B23.12, J112.12
unnamed: B23.13, J112.13
unnamed: B23.20, J112.20
unnamed: B23.23, J113.3
unnamed: B23.24, J113.4
unnamed: B23.29, J113.9
unnamed: B23.31, J113.11
unnamed: B23.32, J113.12
unnamed: B23.33, J113.13
unnamed: J111.RSV1, R265.1
unnamed: J111.RSV2, R266.1
unnamed: B23.30, J113.10
unnamed: B23.17, J112.17
unnamed: B23.16, J112.16
unnamed: B23.19, J112.19
unnamed: B23.10, J112.10
unnamed: B23.14, J112.14
unnamed: D24.A, R279.1
unnamed: B24.6, J117.6
unnamed: B24.8, J117.8
unnamed: B24.9, J117.9
unnamed: B24.11, J117.11
unnamed: B24.12, J117.12
unnamed: B24.13, J117.13
unnamed: B24.20, J117.20
unnamed: B24.23, J118.3
unnamed: B24.24, J118.4
unnamed: B24.29, J118.9
unnamed: B24.31, J118.11
unnamed: B24.32, J118.12
unnamed: B24.33, J118.13
unnamed: J116.RSV1, R277.1
unnamed: J116.RSV2, R278.1
unnamed: B24.30, J118.10
unnamed: B24.17, J117.17
unnamed: B24.16, J117.16
unnamed: B24.19, J117.19
unnamed: B24.10, J117.10
unnamed: B24.14, J117.14
unnamed: D25.A, R291.1
unnamed: B25.6, J122.6
unnamed: B25.8, J122.8
unnamed: B25.9, J122.9
unnamed: B25.11, J122.11
unnamed: B25.12, J122.12
unnamed: B25.13, J122.13
unnamed: B25.20, J122.20
unnamed: B25.23, J123.3
unnamed: B25.24, J123.4
unnamed: B25.29, J123.9
unnamed: B25.31, J123.11
unnamed: B25.32, J123.12
unnamed: B25.33, J123.13
unnamed: J121.RSV1, R289.1
unnamed: J121.RSV2, R290.1
unnamed: B25.30, J123.10
unnamed: B25.17, J122.17
unnamed: B25.16, J122.16
unnamed: B25.19, J122.19
unnamed: B25.10, J122.10
unnamed: B25.14, J122.14
SCL: B1.25, J3.5, R14.1, U1.2
SCL1: B2.25, J8.5, R21.1, U2.2
SCL2: B3.25, J13.5, R33.1, U3.2
SCL3: B4.25, J18.5, R45.1, U4.2
SCL4: B5.25, J23.5, R57.1, U5.2
SCL5: B6.25, J28.5, R69.1, U6.2
SCL6: B7.25, J33.5, R81.1, U7.2
SCL7: B8.25, J38.5, R93.1, U8.2
SCL8: B9.25, J43.5, R105.1, U9.2
SCL9: B10.25, J48.5, R117.1, U10.2
SCL10: B11.25, J53.5, R129.1, U11.2
SCL11: B12.25, J58.5, R141.1, U12.2
SCL12: B13.25, J63.5, R153.1, U13.2
SCL13: B14.25, J68.5, R165.1, U14.2
SCL14: B15.25, J73.5, R177.1, U15.2
SCL15: B16.25, J78.5, R189.1, U16.2
SCL16: B17.25, J83.5, R201.1, U17.2
SCL17: B18.25, J88.5, R213.1, U18.2
SCL18: B19.25, J93.5, R225.1, U19.2
SCL19: B20.25, J98.5, R237.1, U20.2
SCL20: B21.25, J103.5, R249.1, U21.2
SCL21: B22.25, J108.5, R261.1, U22.2
SCL22: B23.25, J113.5, R273.1, U23.2
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
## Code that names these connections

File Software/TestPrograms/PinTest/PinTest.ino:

#include <Arduino.h>

#define AUX_LED_PIN 13
#define GPS_TX_PIN 16
#define GPS_RX_PIN 17
#define SD_SCK_PIN 18
#define SD_DO_PIN 19
#define SD_DI_PIN 23
#define SD_CS_PIN 33
#define SD_CD_PIN 38
#define IMU_SDA_PIN 21
#define IMU_SCL_PIN 22

void setup(){
    Serial.begin(115200);

	pinMode(AUX_LED_PIN, OUTPUT);
	digitalWrite(AUX_LED_PIN, 1);

	pinMode(SD_CD_PIN, INPUT);

	Serial.println("Sketch Started.");
	Serial.println("D13 LED should be blinking.");

}

void loop(){
	delay(1000);
	Serial.print("CD Inserted? -- ");
	if(digitalRead(SD_CD_PIN) == 1)
	{
		Serial.println("Yes.");
	}
	else
	{
		Serial.println("No.");
	}

	digitalWrite(AUX_LED_PIN, digitalRead(AUX_LED_PIN)^0x01);
}

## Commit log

2017-08-04 Preliminary design complete
2017-08-07 Checked DRC, ready for kickoff
2017-08-07 Switched to other GPS jack
2017-08-08 Ready for review
2017-08-08 Ready for QC review
2017-08-08 Fixed v01 check issues
2017-09-18 Reviewing for reds
2017-09-19 Finished proto v01 test doc
2017-09-19 Double checked layout vs. fixed proto. Adjusted small shapes.
2017-09-22 Fixed items from redboard review
2017-10-03 panel
2017-10-31 Polishing examples
2017-11-01 Removed v01 design
2017-11-07 Finished examples
2017-11-16 Formatted readme for release
2018-09-13 Update GPS_SerialPassThrough.ino
    Modify the variable " HardwareSerial Serial2(2); " because it does not compile, change the vairbale to " HardwareSerial GPS(2); "
2020-02-27 Update Software Folder for Library Updates
    Updated examples to add compatibility with latest versions of LSM9DS1 and BME280 libraries along with ESP32 Arduino Core.
    Add calls to Wire.begin(); and updated sensor init functions to latest versions of libraries.
    Fixed Serial1 calls to work with latest version of ESP32 Arduino Core.
    Removed MISC examples as they are outdated.
2020-02-27 Update Readme
    Old readme was just a template.
2020-02-27 Update Readme
    Update Readme to link to v1.0.0a release for Software Update.
2020-02-27 Update LSM9DS1_CSV Example
    Cleaning up commented out code from old version.
2020-02-27 Cleaning up outdated comments
    Cleaning up the comments in the BMEIMU.ino, GPS_Parser.ino and SD_Test_Motion_Board.ino examples.
